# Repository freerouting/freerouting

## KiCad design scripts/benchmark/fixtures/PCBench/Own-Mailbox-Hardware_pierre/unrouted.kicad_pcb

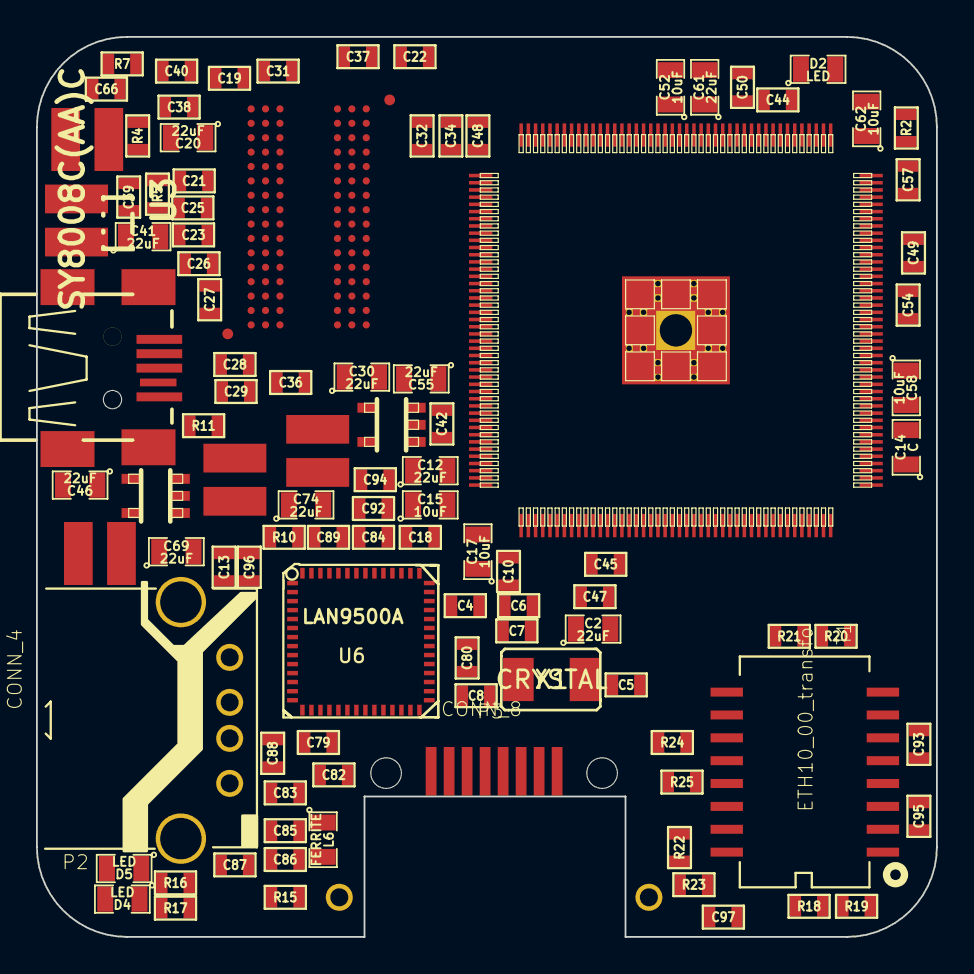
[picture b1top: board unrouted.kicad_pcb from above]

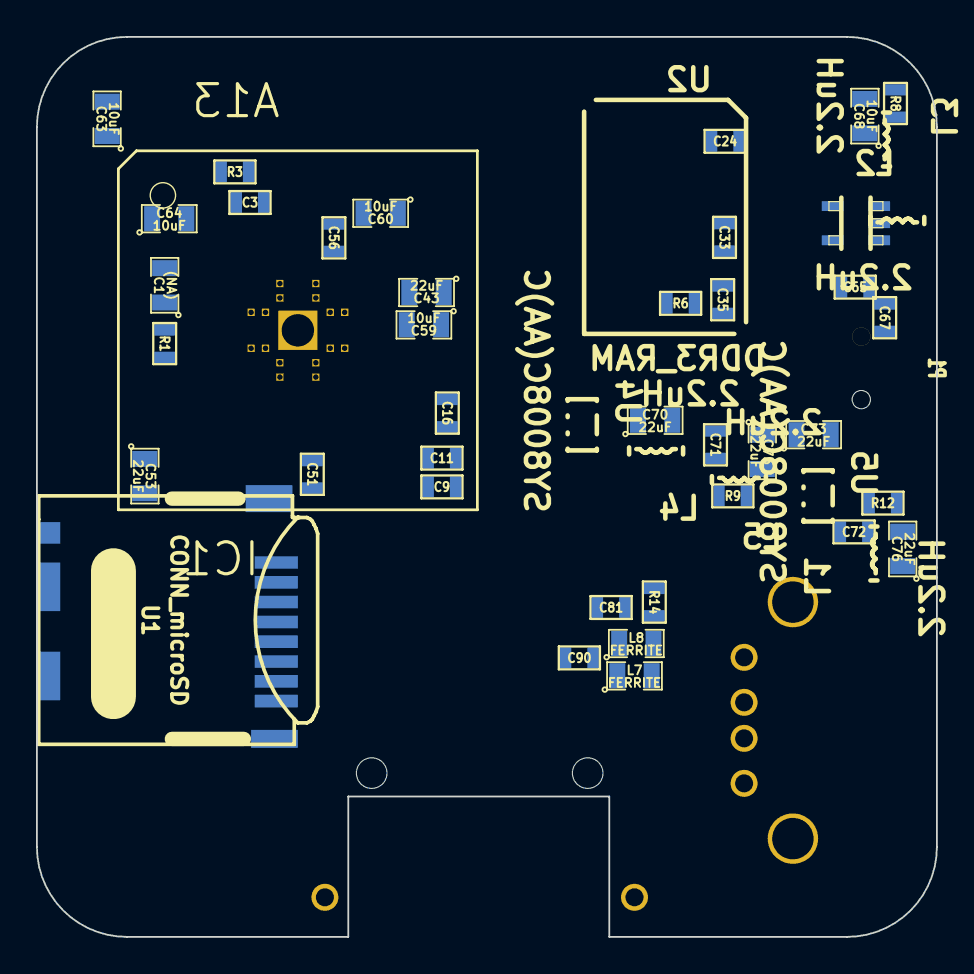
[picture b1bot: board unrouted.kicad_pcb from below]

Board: 4 copper layers, 50.0 x 50.0 mm, 141 parts (38 on the bottom side), 113 nets, no tracks yet.

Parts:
C1: (NA); SM0805
C2, C12, C20, C30, C41, C43, C46, C53, C55, C61, C69, C70, C73, C74, C75, C76: 22uF; SM0805
C3, C4, C13, C16, C18, C19, C21, C22, C23, C24, C25, C26, C27, C28, C29, C31, C32, C33, C34, C35, C36, C37, C38, C39, C40, C42, C44, C45, C47, C48, C49, C50, C51, C54, C56, C57, C79, C80, C81, C82, C83, C84, C85, C86, C87, C88, C92, C93, C94, C95, C96: 100nF; SM0603
C5, C8, C90: 10pF; SM0603
C6, C7, C9, C10: 1nF; SM0603
C11, C89, C97: 1uF; SM0603
C14: C; SM0805
C15, C17, C52, C58, C59, C60, C62, C63, C64, C68: 10uF; SM0805
C65, C71, C72: 22pF; SM0603
C66, C67: 22uF; SM0603
D2, D4, D5: LED; SM0805
IC1: A13; TQFP176
L1, L2, L3, L4, L5: 2.2uH; CD32
L6, L7, L8: FERRITE; SM0805
P1: CONN_4; CONN_USB_MINI_PIERRE
P2: CONN_4; USB-A_TH
P3: CONN_8; RJ45_LP_RA_SMT
R1: 47k; SM0603
R2: 500R; SM0603
R3: 240R; SM0603
R4, R5: 1k(1%); SM0603
R6: 240R(1%); SM0603
R7: 2k(1%); SM0603
R8: 1.5k(1%); SM0603
R9: 100k(1%); SM0603
R10: 22k(1%); SM0603
R11: 4.99k(1%); SM0603
R12: 3.3k(1%); SM0603
R14, R15: R; SM0603
R16, R17: 100R; SM0603
R18, R19, R20, R21: 50R; SM0603
R22, R23, R24, R25: 75R; SM0603
T1: ETH10_00_transfo; H1601CG
U1: CONN_microSD; Memory_Card_microSD_DM3CS-SF
U2: DDR3_RAM; FBGA96
U3, U4, U5: SY8008C(AA)C; SOT23-5
U6: LAN9500A; QFN48
X1: CRYSTAL; SMDXTAL24mhz

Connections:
1V5: C19.1, C20.1, C21.1, C22.1, C23.1, C24.1, C25.1, C26.1, C27.1, C28.1, C29.1, C30.1, C31.1, C32.1, C33.1, C34.1, C35.1, C36.1, C37.1, C38.1, C39.1, C43.1, C48.1, C52.1, C56.1, C59.1, C72.1, C74.1, C76.1, IC1.23, IC1.30, IC1.43, IC1.53, IC1.62, L5.2, R5.1, R11.1, U2.A1, U2.B2, U2.C1, U2.C9, U2.D2, U2.D9, U2.E9, U2.F1, U2.H2, U2.H9, U2.K2, U2.N1, U2.R1, U2.R9
3VA: C12.2, IC1.81
+5V: C41.1, C46.1, C69.1, C70.1, L1.2, P1.1, U3.1, U3.4, U4.1, U4.4, U5.1, U5.4
/Erhernet/RX+: P3.7, T1.11
/Erhernet/RX-: P3.8, T1.9
/Erhernet/TX+: P3.3, T1.16
/Erhernet/TX-: P3.6, T1.14
DDR3_A00: IC1.64, U2.N3
DDR3_A01: IC1.52, U2.P7
DDR3_A03: IC1.65, U2.N2
DDR3_A04: IC1.51, U2.P8
DDR3_A05: IC1.67, U2.P2
DDR3_A06: IC1.54, IC1.66, U2.R8
DDR3_A07: IC1.71, U2.R2
DDR3_A08: IC1.55, U2.T8
DDR3_A09: IC1.69, U2.R3
DDR3_A10: IC1.48, U2.L7
DDR3_A11: IC1.56, U2.R7
DDR3_A12: IC1.50, U2.N7
DDR3_A13: IC1.68, U2.T3
DDR3_BA0: IC1.63, U2.M2
DDR3_BA1: IC1.49, U2.N8
DDR3_BA2: IC1.61, U2.M3
DDR3_CAS: IC1.59, U2.K3
DDR3_CK: IC1.45, U2.J7
DDR3_CKE: IC1.47, U2.K9
DDR3_CK_N: IC1.46, U2.K7
DDR3_D00: IC1.22, U2.E3
DDR3_D01: IC1.40, U2.F7
DDR3_D02: IC1.21, U2.F2
DDR3_D03: IC1.41, U2.F8
DDR3_D04: IC1.19, U2.H3
DDR3_D05: IC1.44, U2.H8
DDR3_D06: IC1.20, U2.G2
DDR3_D07: IC1.42, U2.H7
DDR3_D08: IC1.37, U2.D7
DDR3_D09: IC1.25, U2.C3
DDR3_D10: IC1.39, U2.C8
DDR3_D11: IC1.24, U2.C2
DDR3_D12: IC1.36, U2.A7
DDR3_D13: IC1.26, U2.A2
DDR3_D14: IC1.38, U2.B8
DDR3_D15: IC1.27, U2.A3
DDR3_DM0: IC1.29, U2.E7
DDR3_DM1: IC1.28, U2.D3
DDR3_DQS0: IC1.31, U2.F3
DDR3_DQS0_N: IC1.32, U2.G3
DDR3_DQS1: IC1.33, U2.C7
DDR3_DQS1_N: IC1.34, U2.B7
DDR3_ODT: IC1.72, U2.K1
DDR3_RAS: IC1.58, U2.J3
DDR3_RST: IC1.70, U2.T2
DDR3_WE: IC1.60, U2.L3
GND: C1.2, C2.2, C3.2, C4.1, C5.1, C6.1, C7.1, C8.1, C9.1, C10.1, C11.1, C12.1, C13.2, C14.1, C15.1, C16.1, C17.1, C18.1, C19.2, C20.2, C21.2, C22.2, C23.2, C24.2, C25.2, C26.2, C27.2, C28.2, C29.2, C30.2, C31.2, C32.2, C33.2, C34.2, C35.2, C36.2, C37.2, C38.2, C40.2, C41.2, C42.2, C43.2, C44.2, C45.2, C46.2, C47.2, C48.2, C49.2, C50.2, C51.2, C52.2, C53.2, C54.2, C55.2, C56.2, C57.2, C58.2, C59.2, C60.2, C61.2, C62.2, C63.2, C64.2, C66.2, C67.2, C68.2, C69.2, C70.2, C73.2, C74.2, C75.2, C76.2, C79.2, C80.2, C81.2, C82.2, C83.2, C84.2, C85.2, C86.2, C87.2, C88.2, C89.2, C90.1, C92.2, C93.1, C94.2, C95.2, C96.2, C97.1, IC1.79, P1.4, P2.4, R2.2, R3.2, R4.2, R6.2, R8.2, R10.2, R12.2, R14.1, R15.1, U1.6, U1.9, U2.A9, U2.B1, U2.B3, U2.B9, U2.D1, U2.D8, U2.E1, U2.E2, U2.E8, U2.F9, U2.G1, U2.G8, U2.G9, U2.J2, U2.J8, U2.L2, U2.M1, U2.M9, U2.P1, U2.P9, U2.T1, U2.T9, U3.2, U4.2, U5.2, U6.13, U6.33
LED1: D4.2, U6.27
LED2: D5.2, U6.28
unnamed: C1.1, IC1.159
unnamed: C3.1, IC1.18
unnamed: C6.2, IC1.90
unnamed: C7.2, IC1.89
unnamed: C9.2, IC1.88
unnamed: C10.2, IC1.87
unnamed: C11.2, IC1.83
unnamed: C13.1, L1.1, P2.1
unnamed: C15.2, C16.2, IC1.80
unnamed: C17.2, C18.2, IC1.82
unnamed: C39.2, C40.1, R4.1, R5.2, U2.H1, U2.M8
unnamed: C65.2, R7.2, R8.1, U3.5
unnamed: C71.2, R9.2, R10.1, U4.5
unnamed: C72.2, R11.2, R12.1, U5.5
unnamed: C90.2, U6.19
unnamed: C97.2, R22.1, R23.1, R24.1, R25.1
unnamed: D2.1, IC1.12
unnamed: D2.2, R2.1
unnamed: D4.1, R17.1
unnamed: D5.1, R16.1
unnamed: IC1.17, R3.1
unnamed: IC1.158, R1.2
unnamed: L2.1, U3.3
unnamed: L4.1, U4.3
unnamed: L5.1, U5.3
unnamed: P3.1, P3.2, R25.2
unnamed: P3.4, P3.5, R23.2
unnamed: R6.1, U2.L8
unnamed: R14.2, U6.8
unnamed: R15.2, U6.16
unnamed: R22.2, T1.15
unnamed: R24.2, T1.10
RPX_N: R20.1, T1.8, U6.5
RPX_P: R21.1, T1.6, U6.6
SDC0_CLK: IC1.110, U1.5
SDC0_CMD: IC1.111, U1.3
SDC0_D0: IC1.108, U1.7
SDC0_D1: IC1.107, U1.8
SDC0_D2: IC1.113, U1.1
SDC0_D3: IC1.112, U1.2
TPX_N: R19.2, T1.3, U6.2
TPX_P: R18.2, T1.1, U6.3
UART1_RX: IC1.151, P1.3
UART1_TX: IC1.152, P1.2
USB_ETH_N: IC1.93, U6.11
USB_ETH_P: IC1.94, U6.12
USB_HOST_N: IC1.95, P2.2
USB_HOST_P: IC1.96, P2.3
VCC: C2.1, C4.2, C14.2, C42.1, C47.1, C49.1, C53.1, C71.1, C73.1, C75.1, C79.1, C80.1, C81.1, C82.1, C84.1, C93.2, C95.1, IC1.76, IC1.97, IC1.100, IC1.142, IC1.163, L4.2, L6.1, R9.1, R16.2, R17.2, R18.1, R19.1, R20.2, R21.2, T1.7, U1.4, U6.20, U6.24, U6.25, U6.35, U6.48, U6.49, U6.51, U6.52
VDD33A: C83.1, C85.1, C86.1, C87.1, L6.2, U6.4, U6.7, U6.9, U6.15
VDDBUSPLL: C88.1, L7.2, U6.17
VDDCORE: C89.1, C92.1, C94.1, L7.1, L8.1, U6.21, U6.50
VDDPLL: C96.1, L8.2, U6.10
VDD_CPU: C44.1, C50.1, C54.1, C57.1, C61.1, C62.1, C63.1, C64.1, C65.1, C66.1, C67.1, IC1.9, IC1.11, IC1.16, IC1.156, IC1.164, IC1.169, IC1.173, L2.2, L3.1, R7.1
VDD_INT: C45.1, C51.1, C55.1, C58.1, C60.1, C68.1, IC1.35, IC1.73, IC1.98, IC1.109, IC1.149, L3.2
X1_N: C5.2, IC1.92, X1.1
X1_P: C8.2, IC1.91, X1.2

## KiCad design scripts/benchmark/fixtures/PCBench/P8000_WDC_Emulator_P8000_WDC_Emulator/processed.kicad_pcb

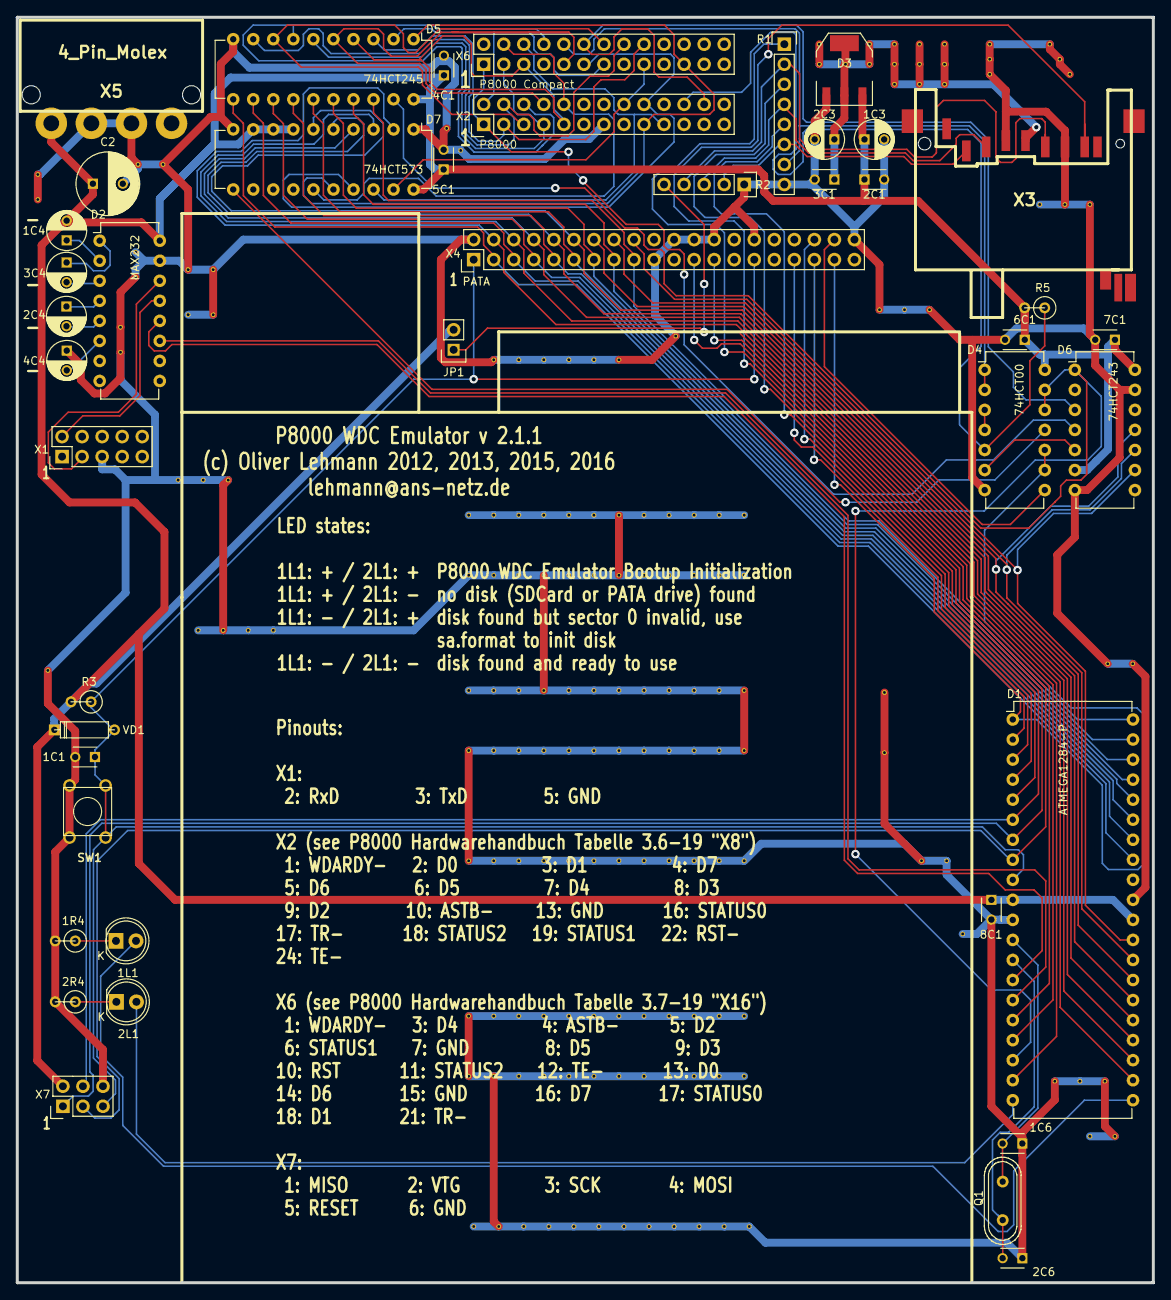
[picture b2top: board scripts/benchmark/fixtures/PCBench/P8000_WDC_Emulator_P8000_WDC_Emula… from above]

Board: 2 copper layers, 144.0 x 160.4 mm, 214 parts (0 on the bottom side), 72 nets.

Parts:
1C1, 2C1, 3C1, 4C1, 5C1, 6C1, 7C1, 8C1: 100n; C_Disc_D3_P2.5
1C3, 2C3: 100u; C_Radial_D5_L6_P2.5
1C4, 2C4, 3C4, 4C4: 1u; C_Radial_D5_L6_P2.5
1C6, 2C6: 22p; C_Disc_D3_P2.5
1L1, 2L1: LED; LED-5MM
1R4, 2R4: 300; R1
C2: 470u; C_Radial_D8_L13_P3.8
D1: ATMEGA1284-P; DIP-40_W15.24mm
D2: MAX232; DIP-16_W7.62mm
D3: TS1117 BCW33; SOT-223
D4: 74HCT00; DIP-14_W7.62mm
D5: 74HCT245; DIP-20_W7.62mm
D6: 74HCT243; DIP-14_W7.62mm
D7: 74HCT573; DIP-20_W7.62mm
Hole-Inner-1, Hole-Inner-2, Hole-Inner-3, Hole-Inner-4: VAL**; HOLE_4x8mm_4mmclear_pad
Hole-Outer-1, Hole-Outer-2, Hole-Outer-3, Hole-Outer-4: VAL**; HOLE_4x8mm_pad
JP1: JUMPER; Pin_Header_Straight_1x02
Q1: CRYSTAL; Crystal_HC49-U_Vertical
R1: 1k8; Pin_Header_Straight_1x08
R2: 3k3; Pin_Header_Straight_1x05
R3: 10k; R1
R5: 4k7; R1
SW1: SW_PUSH; SW_6x6
VD1: 1N4148; D3
VIA-0.6mm, VIA-0.6mm_2, VIA-0.6mm_3, VIA-0.6mm_4, VIA-0.6mm_5, VIA-0.6mm_6, VIA-0.6mm_7, VIA-0.6mm_8, VIA-0.6mm_9, VIA-0.6mm_10, VIA-0.6mm_11, VIA-0.6mm_12, VIA-0.6mm_13, VIA-0.6mm_14, VIA-0.6mm_15, VIA-0.6mm_16, VIA-0.6mm_17, VIA-0.6mm_18, VIA-0.6mm_19, VIA-0.6mm_20, VIA-0.6mm_21, VIA-0.6mm_22, VIA-0.6mm_23, VIA-0.6mm_24, VIA-0.6mm_25, VIA-0.6mm_26, VIA-0.6mm_27, VIA-0.6mm_28, VIA-0.6mm_29, VIA-0.6mm_30, VIA-0.6mm_31, VIA-0.6mm_32, VIA-0.6mm_33, VIA-0.6mm_34, VIA-0.6mm_35, VIA-0.6mm_36, VIA-0.6mm_37, VIA-0.6mm_38, VIA-0.6mm_39, VIA-0.6mm_40, VIA-0.6mm_41, VIA-0.6mm_42, VIA-0.6mm_43, VIA-0.6mm_44, VIA-0.6mm_45, VIA-0.6mm_46, VIA-0.6mm_47, VIA-0.6mm_48, VIA-0.6mm_49, VIA-0.6mm_50, VIA-0.6mm_51, VIA-0.6mm_52, VIA-0.6mm_53, VIA-0.6mm_54, VIA-0.6mm_55, VIA-0.6mm_56, VIA-0.6mm_57, VIA-0.6mm_58, VIA-0.6mm_59, VIA-0.6mm_60, VIA-0.6mm_61, VIA-0.6mm_62, VIA-0.6mm_63, VIA-0.6mm_64, VIA-0.6mm_65, VIA-0.6mm_66, VIA-0.6mm_67, VIA-0.6mm_68, VIA-0.6mm_69, VIA-0.6mm_70, VIA-0.6mm_71, VIA-0.6mm_72, VIA-0.6mm_73, VIA-0.6mm_74, VIA-0.6mm_75, VIA-0.6mm_76, VIA-0.6mm_77, VIA-0.6mm_78, VIA-0.6mm_79, VIA-0.6mm_80, VIA-0.6mm_81, VIA-0.6mm_82, VIA-0.6mm_83, VIA-0.6mm_84, VIA-0.6mm_85, VIA-0.6mm_86, VIA-0.6mm_87, VIA-0.6mm_88, VIA-0.6mm_89, VIA-0.6mm_90, VIA-0.6mm_91, VIA-0.6mm_92, VIA-0.6mm_93, VIA-0.6mm_94, VIA-0.6mm_95, VIA-0.6mm_96, VIA-0.6mm_97, VIA-0.6mm_98, VIA-0.6mm_99, VIA-0.6mm_100, VIA-0.6mm_101, VIA-0.6mm_102, VIA-0.6mm_103, VIA-0.6mm_104, VIA-0.6mm_105, VIA-0.6mm_106, VIA-0.6mm_107, VIA-0.6mm_108, VIA-0.6mm_109, VIA-0.6mm_110, VIA-0.6mm_111, VIA-0.6mm_112, VIA-0.6mm_113, VIA-0.6mm_114, VIA-0.6mm_115, VIA-0.6mm_116, VIA-0.6mm_117, VIA-0.6mm_118, VIA-0.6mm_119, VIA-0.6mm_120, VIA-0.6mm_121, VIA-0.6mm_122, VIA-0.6mm_123, VIA-0.6mm_124, VIA-0.6mm_125, VIA-0.6mm_126, VIA-0.6mm_127, VIA-0.6mm_128, VIA-0.6mm_129, VIA-0.6mm_130, VIA-0.6mm_131, VIA-0.6mm_132, VIA-0.6mm_133, VIA-0.6mm_134, VIA-0.6mm_135, VIA-0.6mm_136, VIA-0.6mm_137, VIA-0.6mm_138, VIA-0.6mm_139, VIA-0.6mm_140, VIA-0.6mm_141, VIA-0.6mm_142, VIA-0.6mm_143, VIA-0.6mm_144, VIA-0.6mm_145, VIA-0.6mm_146, VIA-0.6mm_147, VIA-0.6mm_148, VIA-0.6mm_149, VIA-0.6mm_150, VIA-0.6mm_151, VIA-0.6mm_152, VIA-0.6mm_153, VIA-0.6mm_154, VIA-0.6mm_155, VIA-0.6mm_156, VIA-0.6mm_157, VIA-0.6mm_158, VIA-0.6mm_159, VIA-0.6mm_160, VIA-0.6mm_161, VIA-0.6mm_162, VIA-0.6mm_163: VAL**; VIA-0.6mm
X1: RS-232; Pin_Header_Straight_2x05
X2: P8000; Pin_Header_Straight_2x13
X3: SD-CON; sd_cocket_yamaichi_fps009_3001
X4: PATA; Pin_Header_Straight_2x20
X5: 4_Pin_Molex; 4PIN_MOLEX
X6: P8000-Compact; Pin_Header_Straight_2x13
X7: AVR-ISP-6; Pin_Header_Straight_2x03

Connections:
+3V3: 2C3.1, 3C1.1, D3.2, VIA-0.6mm_117.1, VIA-0.6mm_118.1, VIA-0.6mm_119.1, VIA-0.6mm_120.1, VIA-0.6mm_121.1, VIA-0.6mm_122.1, VIA-0.6mm_123.1, VIA-0.6mm_124.1, VIA-0.6mm_125.1, VIA-0.6mm_126.1, VIA-0.6mm_127.1, VIA-0.6mm_128.1, VIA-0.6mm_129.1, VIA-0.6mm_130.1, X3.4
//ASTB: D7.15, X2.10, X6.4
//CS0: D1.1, D4.9, D4.10, X4.37
//RD: D1.17, X4.25
//RDY: D6.4, X2.1, X6.1
//RST2: D4.5, R5.1, X2.22
//TE: D6.3, X2.24, X6.12
//TR: D5.1, D7.16, X2.17, X6.21
//WR: D1.16, X4.23
/D0: D5.2, X2.2, X6.13
/D1: D5.3, X2.3, X6.18
/D2: D5.4, X2.9, X6.5
/D3: D5.5, X2.8, X6.9
/D4: D5.6, X2.7, X6.3
/D5: D5.7, X2.6, X6.8
/D6: D5.8, X2.5, X6.14
/D7: D5.9, X2.4, X6.16
/DA0: D1.2, X4.35
/DA1: D1.3, X4.33
/DA2: D1.4, X4.36
/PA0: D1.40, D5.18, X4.17
/PA1: D1.39, D5.17, X4.15
/PA2: D1.38, D5.16, X4.13
/PA3: D1.37, D5.15, X4.11
/PA4: D1.36, D5.14, X4.9
/PA5: D1.35, D5.13, X4.7
/PA6: D1.34, D5.12, X4.5
/PA7: D1.33, D5.11, X4.3
/PC0: D1.22, D7.2, X4.4
/PC1: D1.23, D7.3, X4.6
/PC2: D1.24, D7.4, X4.8
/PC3: D1.25, D7.5, X4.10
/PC4: D1.26, D7.6, X4.12
/PC5: D1.27, D6.11, X4.14
/PC6: D1.28, D6.10, X4.16
/PC7: D1.29, D6.9, X4.18
/RST: D4.6, D6.5
/RST1: D4.1, D4.2, R1.7, X6.10
/STATUS0: D7.19, X2.16, X6.17
/STATUS1: D7.18, X2.19, X6.6
/STATUS2: D7.17, X2.18, X6.11
GND: 1C1.2, 1C3.2, 1C6.1, 1R4.2, 2C1.2, 2C3.2, 2C6.1, 2R4.2, 3C1.2, 4C1.2, 4C4.1, 5C1.2, 6C1.2, 7C1.2, 8C1.2, C2.2, D1.11, D1.31, D2.15, D3.1, D4.7, D5.10, D6.7, D6.13, D7.1, D7.10, R1.8, R2.1, SW1.2, VIA-0.6mm.1, VIA-0.6mm_2.1, VIA-0.6mm_3.1, VIA-0.6mm_4.1, VIA-0.6mm_5.1, VIA-0.6mm_6.1, VIA-0.6mm_7.1, VIA-0.6mm_8.1, VIA-0.6mm_9.1, VIA-0.6mm_10.1, VIA-0.6mm_11.1, VIA-0.6mm_12.1, VIA-0.6mm_13.1, VIA-0.6mm_14.1, VIA-0.6mm_15.1, VIA-0.6mm_16.1, VIA-0.6mm_17.1, VIA-0.6mm_18.1, VIA-0.6mm_19.1, VIA-0.6mm_20.1, VIA-0.6mm_21.1, VIA-0.6mm_22.1, VIA-0.6mm_23.1, VIA-0.6mm_24.1, VIA-0.6mm_25.1, VIA-0.6mm_26.1, VIA-0.6mm_27.1, VIA-0.6mm_28.1, VIA-0.6mm_29.1, VIA-0.6mm_30.1, VIA-0.6mm_31.1, VIA-0.6mm_32.1, VIA-0.6mm_33.1, VIA-0.6mm_34.1, VIA-0.6mm_35.1, VIA-0.6mm_36.1, VIA-0.6mm_37.1, VIA-0.6mm_38.1, VIA-0.6mm_39.1, VIA-0.6mm_40.1, VIA-0.6mm_41.1, VIA-0.6mm_42.1, VIA-0.6mm_43.1, VIA-0.6mm_44.1, VIA-0.6mm_45.1, VIA-0.6mm_46.1, VIA-0.6mm_47.1, VIA-0.6mm_48.1, VIA-0.6mm_49.1, VIA-0.6mm_50.1, VIA-0.6mm_51.1, VIA-0.6mm_52.1, VIA-0.6mm_53.1, VIA-0.6mm_54.1, VIA-0.6mm_55.1, VIA-0.6mm_56.1, VIA-0.6mm_57.1, VIA-0.6mm_58.1, VIA-0.6mm_59.1, VIA-0.6mm_60.1, VIA-0.6mm_61.1, VIA-0.6mm_62.1, VIA-0.6mm_63.1, VIA-0.6mm_64.1, VIA-0.6mm_65.1, VIA-0.6mm_66.1, VIA-0.6mm_67.1, VIA-0.6mm_68.1, VIA-0.6mm_69.1, VIA-0.6mm_70.1, VIA-0.6mm_71.1, VIA-0.6mm_72.1, VIA-0.6mm_73.1, VIA-0.6mm_74.1, VIA-0.6mm_75.1, VIA-0.6mm_76.1, VIA-0.6mm_77.1, VIA-0.6mm_78.1, VIA-0.6mm_79.1, VIA-0.6mm_80.1, VIA-0.6mm_81.1, VIA-0.6mm_82.1, VIA-0.6mm_83.1, VIA-0.6mm_84.1, VIA-0.6mm_85.1, VIA-0.6mm_86.1, VIA-0.6mm_87.1, VIA-0.6mm_88.1, VIA-0.6mm_89.1, VIA-0.6mm_90.1, VIA-0.6mm_91.1, VIA-0.6mm_92.1, VIA-0.6mm_93.1, VIA-0.6mm_94.1, VIA-0.6mm_95.1, VIA-0.6mm_96.1, VIA-0.6mm_97.1, VIA-0.6mm_98.1, VIA-0.6mm_99.1, VIA-0.6mm_100.1, VIA-0.6mm_101.1, VIA-0.6mm_102.1, VIA-0.6mm_103.1, VIA-0.6mm_104.1, VIA-0.6mm_105.1, VIA-0.6mm_106.1, VIA-0.6mm_107.1, VIA-0.6mm_108.1, VIA-0.6mm_109.1, VIA-0.6mm_110.1, VIA-0.6mm_111.1, VIA-0.6mm_112.1, VIA-0.6mm_113.1, VIA-0.6mm_114.1, VIA-0.6mm_115.1, VIA-0.6mm_116.1, VIA-0.6mm_131.1, VIA-0.6mm_132.1, VIA-0.6mm_133.1, VIA-0.6mm_134.1, VIA-0.6mm_135.1, VIA-0.6mm_136.1, VIA-0.6mm_137.1, VIA-0.6mm_138.1, VIA-0.6mm_139.1, VIA-0.6mm_140.1, VIA-0.6mm_141.1, VIA-0.6mm_142.1, VIA-0.6mm_143.1, VIA-0.6mm_144.1, VIA-0.6mm_145.1, VIA-0.6mm_146.1, VIA-0.6mm_147.1, VIA-0.6mm_148.1, VIA-0.6mm_149.1, VIA-0.6mm_150.1, VIA-0.6mm_151.1, VIA-0.6mm_152.1, VIA-0.6mm_153.1, VIA-0.6mm_154.1, VIA-0.6mm_155.1, VIA-0.6mm_156.1, VIA-0.6mm_157.1, VIA-0.6mm_158.1, VIA-0.6mm_159.1, VIA-0.6mm_160.1, VIA-0.6mm_161.1, VIA-0.6mm_162.1, VIA-0.6mm_163.1, X1.5, X2.13, X3.3, X3.6, X4.2, X4.19, X4.22, X4.24, X4.26, X4.30, X4.40, X5.2, X5.3, X7.6
unnamed: 1C1.1, D1.9, R3.1, SW1.1, VD1.2, X4.1, X4.29, X7.5
unnamed: 1C4.1, D2.2
unnamed: 1C6.2, D1.12, Q1.2
unnamed: 1L1.1, 1R4.1
unnamed: 1L1.2, D1.21
unnamed: 2C4.1, D2.4
unnamed: 2C4.2, D2.5
unnamed: 2C6.2, D1.13, Q1.1
unnamed: 2L1.1, 2R4.1
unnamed: 2L1.2, D1.20
unnamed: 3C4.1, D2.1
unnamed: 3C4.2, D2.3
unnamed: 4C4.2, D2.6
unnamed: D1.5, R1.5
unnamed: D1.6, R1.3, X7.4
unnamed: D1.7, X3.7, X7.1
unnamed: D1.8, R1.1, X7.3
unnamed: D1.14, D2.12
unnamed: D1.15, D2.11
unnamed: D1.18, D4.12, D4.13, D5.19, D6.1
unnamed: D1.19, JP1.1, R2.5
unnamed: D2.13, X1.2
unnamed: D2.14, X1.3
unnamed: D4.3, D4.4
unnamed: D4.8, X4.38
unnamed: D4.11, D7.11
unnamed: R1.2, R2.4, X3.5
unnamed: R1.4, R2.3, X3.2
unnamed: R1.6, R2.2, X3.1
VCC: 1C3.1, 1C4.2, 2C1.1, 4C1.1, 5C1.1, 6C1.1, 7C1.1, 8C1.1, C2.1, D1.10, D1.30, D2.16, D3.3, D4.14, D5.20, D6.6, D6.14, D7.7, D7.8, D7.9, D7.20, JP1.2, R3.2, R5.2, VD1.1, X5.1, X7.2

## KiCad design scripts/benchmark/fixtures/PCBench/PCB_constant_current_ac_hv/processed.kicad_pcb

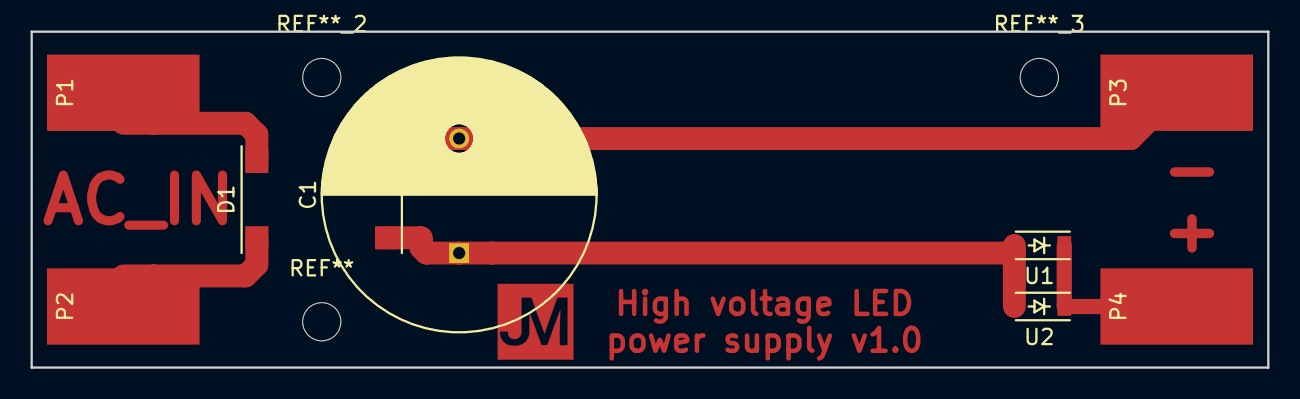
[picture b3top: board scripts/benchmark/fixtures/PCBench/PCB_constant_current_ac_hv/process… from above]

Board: 2 copper layers, 81.0 x 22.0 mm, 8 parts (0 on the bottom side), 5 nets.

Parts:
C1: 120uF@400V; C_Radial_D18_L36_P7.5
D1: DB207S
P1, P2, P3, P4: CONN_01X01; SolderWirePad_single_SMD_5x10mm
U1, U2: NSI45030AT1G; SOD-123

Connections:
/AC_IN1: D1.2, P1.1
/AC_IN2: D1.4, P2.1
/NEG_OUT: C1.2, D1.1, P3.1
/POS_OUT: P4.1, U1.1, U2.1
unnamed: C1.1, D1.3, U1.2, U2.2

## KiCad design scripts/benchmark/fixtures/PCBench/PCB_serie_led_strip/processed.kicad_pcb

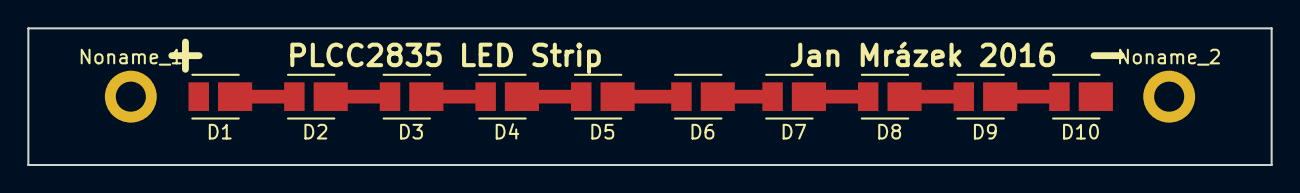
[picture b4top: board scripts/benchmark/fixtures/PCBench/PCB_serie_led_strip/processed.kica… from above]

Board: 2 copper layers, 91.0 x 10.0 mm, 12 parts (0 on the bottom side), 9 nets.

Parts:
D1, D2, D3, D4, D5, D6, D7, D8, D9, D10: LED; LED_PLCC_2835_Handsolder
Noname_1, Noname_2: MountingHole_2.2mm_M2_DIN965_Pad

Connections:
unnamed: D1.1, D2.2
unnamed: D2.1, D3.2
unnamed: D3.1, D4.2
unnamed: D4.1, D5.2
unnamed: D5.1, D6.2
unnamed: D6.1, D7.2
unnamed: D7.1, D8.2
unnamed: D8.1, D9.2
unnamed: D9.1, D10.2

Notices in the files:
parts and their libraries:
Copyright © 2012, Michel Stempin, All rights reserved
Licenced under Creative Commons CC BY-SA 3.0 license.
